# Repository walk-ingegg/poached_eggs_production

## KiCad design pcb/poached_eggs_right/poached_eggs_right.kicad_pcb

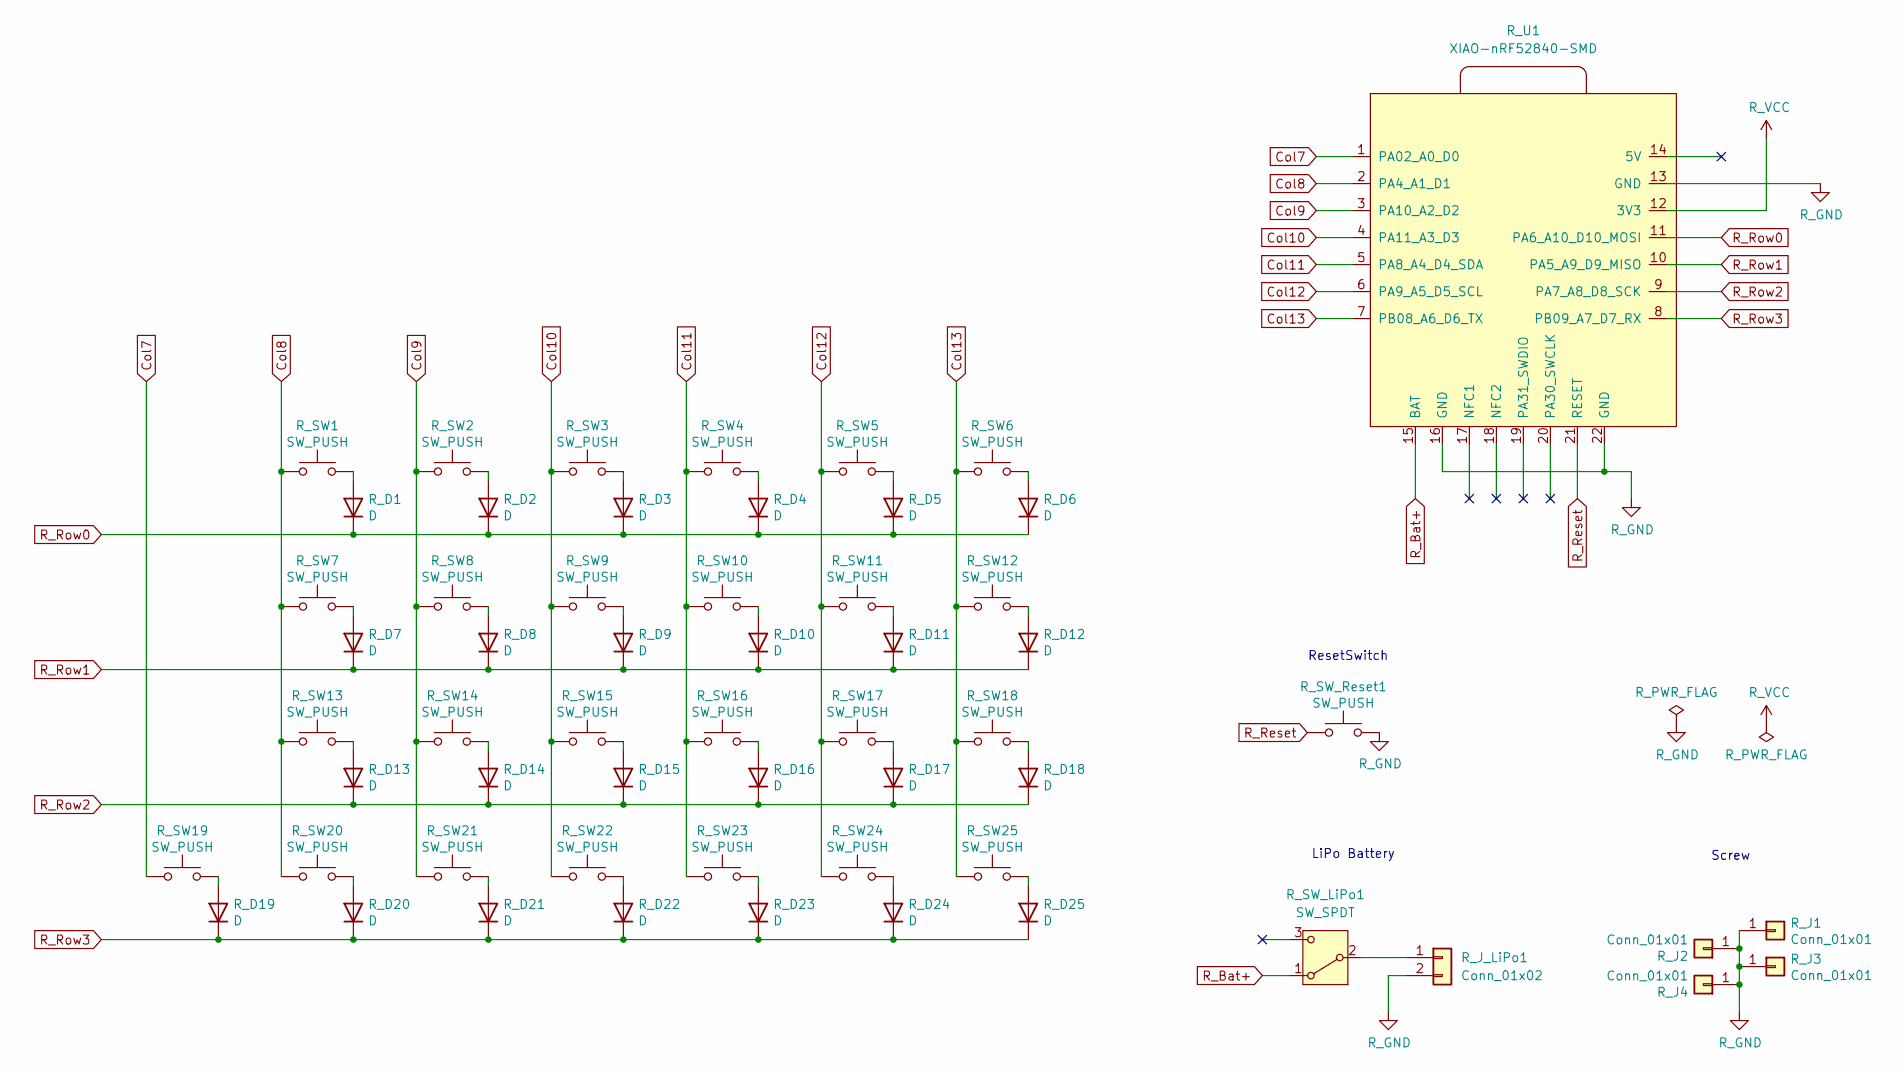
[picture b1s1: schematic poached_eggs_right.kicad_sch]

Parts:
R_D1, R_D2, R_D3, R_D4, R_D5, R_D6, R_D7, R_D8, R_D9, R_D10, R_D11, R_D12, R_D13, R_D14, R_D15, R_D16, R_D17, R_D18, R_D19, R_D20, R_D21, R_D22, R_D23, R_D24, R_D25: D; D_SOD-323
R_J1, R_J2, R_J3, R_J4: Conn_01x01; MountingHole_2.2mm_M2_ISO7380_Pad
R_J_LiPo1: Conn_01x02; JST_PH_S2B-PH-K_02x2.00mm_Angled_3d_wegg
R_SW1, R_SW2, R_SW3, R_SW4, R_SW5, R_SW6, R_SW7, R_SW8, R_SW9, R_SW10, R_SW11, R_SW12, R_SW13, R_SW14, R_SW15, R_SW16, R_SW17, R_SW18, R_SW19, R_SW20, R_SW21, R_SW22, R_SW23, R_SW24, R_SW25: SW_PUSH; Choc_v2_Hotswap_1u_17.5mm
R_SW_LiPo1: SW_SPDT; SW_Slide_SPDT_Angled_CK_OS102011MA1Q
R_SW_Reset1: SW_PUSH; SW_PUSH_1P1T_6x3.5mm_H4.3_APEM_MJTP1243_3d
R_U1: XIAO-nRF52840-SMD; XIAO-nRF52840-SMD_via

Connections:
Col7: R_SW19.1, R_U1.1 (PA02_A0_D0)
Col8: R_SW1.1, R_SW7.1, R_SW13.1, R_SW20.1, R_U1.2 (PA4_A1_D1)
Col9: R_SW2.1, R_SW8.1, R_SW14.1, R_SW21.1, R_U1.3 (PA10_A2_D2)
Col10: R_SW3.1, R_SW9.1, R_SW15.1, R_SW22.1, R_U1.4 (PA11_A3_D3)
Col11: R_SW4.1, R_SW10.1, R_SW16.1, R_SW23.1, R_U1.5 (PA8_A4_D4_SDA)
Col12: R_SW5.1, R_SW11.1, R_SW17.1, R_SW24.1, R_U1.6 (PA9_A5_D5_SCL)
Col13: R_SW6.1, R_SW12.1, R_SW18.1, R_SW25.1, R_U1.7 (PB08_A6_D6_TX)
unnamed: R_D1.2 (A), R_SW1.2
unnamed: R_D2.2 (A), R_SW2.2
unnamed: R_D3.2 (A), R_SW3.2
unnamed: R_D4.2 (A), R_SW4.2
unnamed: R_D5.2 (A), R_SW5.2
unnamed: R_D6.2 (A), R_SW6.2
unnamed: R_D7.2 (A), R_SW7.2
unnamed: R_D8.2 (A), R_SW8.2
unnamed: R_D9.2 (A), R_SW9.2
unnamed: R_D10.2 (A), R_SW10.2
unnamed: R_D11.2 (A), R_SW11.2
unnamed: R_D12.2 (A), R_SW12.2
unnamed: R_D13.2 (A), R_SW13.2
unnamed: R_D14.2 (A), R_SW14.2
unnamed: R_D15.2 (A), R_SW15.2
unnamed: R_D16.2 (A), R_SW16.2
unnamed: R_D17.2 (A), R_SW17.2
unnamed: R_D18.2 (A), R_SW18.2
unnamed: R_D19.2 (A), R_SW19.2
unnamed: R_D20.2 (A), R_SW20.2
unnamed: R_D21.2 (A), R_SW21.2
unnamed: R_D22.2 (A), R_SW22.2
unnamed: R_D23.2 (A), R_SW23.2
unnamed: R_D24.2 (A), R_SW24.2
unnamed: R_D25.2 (A), R_SW25.2
unnamed: R_J_LiPo1.1, R_SW_LiPo1.2 (B)
R_Bat+: R_SW_LiPo1.1 (A), R_U1.15 (BAT)
R_GND: R_J1.1, R_J2.1, R_J3.1, R_J4.1, R_J_LiPo1.2, R_SW_Reset1.2, R_U1.13 (GND), R_U1.16 (GND), R_U1.22 (GND)
R_Reset: R_SW_Reset1.1, R_U1.21 (RESET)
R_Row0: R_D1.1 (K), R_D2.1 (K), R_D3.1 (K), R_D4.1 (K), R_D5.1 (K), R_D6.1 (K), R_U1.11 (PA6_A10_D10_MOSI)
R_Row1: R_D7.1 (K), R_D8.1 (K), R_D9.1 (K), R_D10.1 (K), R_D11.1 (K), R_D12.1 (K), R_U1.10 (PA5_A9_D9_MISO)
R_Row2: R_D13.1 (K), R_D14.1 (K), R_D15.1 (K), R_D16.1 (K), R_D17.1 (K), R_D18.1 (K), R_U1.9 (PA7_A8_D8_SCK)
R_Row3: R_D19.1 (K), R_D20.1 (K), R_D21.1 (K), R_D22.1 (K), R_D23.1 (K), R_D24.1 (K), R_D25.1 (K), R_U1.8 (PB09_A7_D7_RX)
R_VCC: R_U1.12 (3V3)

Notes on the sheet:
Screw
LiPo Battery
ResetSwitch

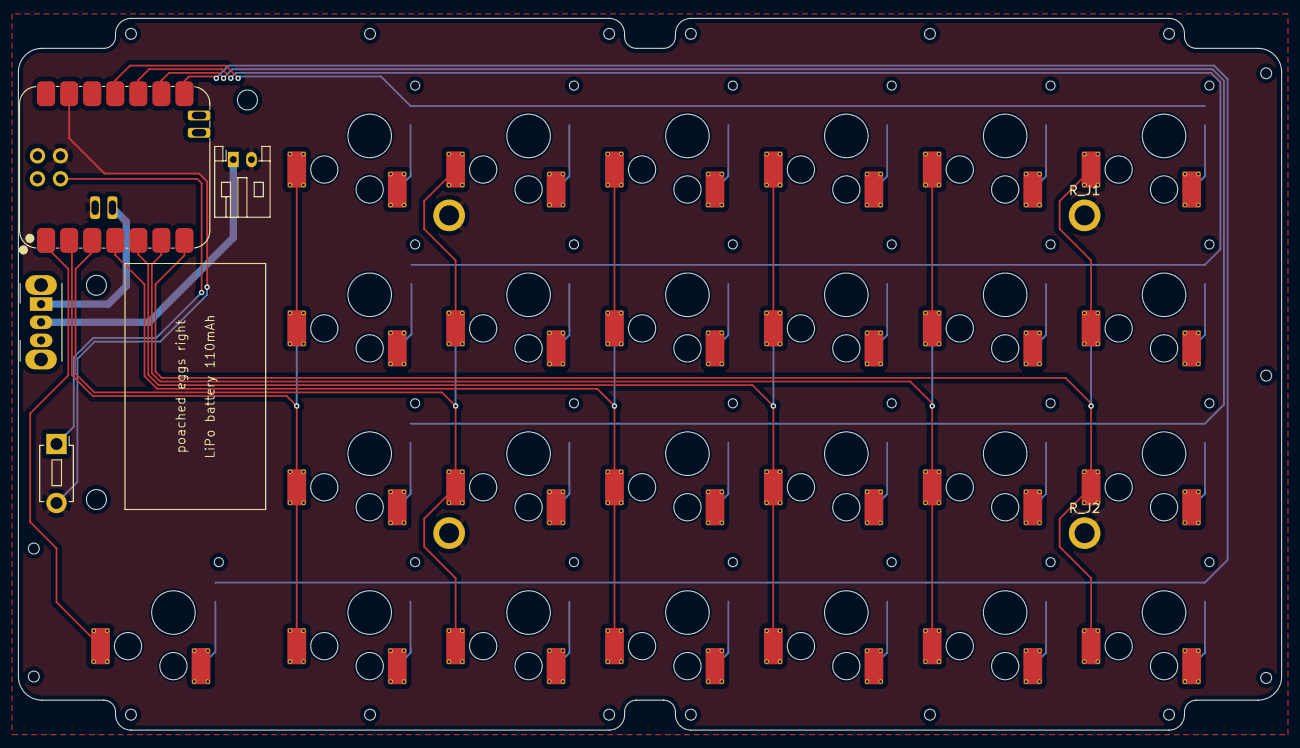
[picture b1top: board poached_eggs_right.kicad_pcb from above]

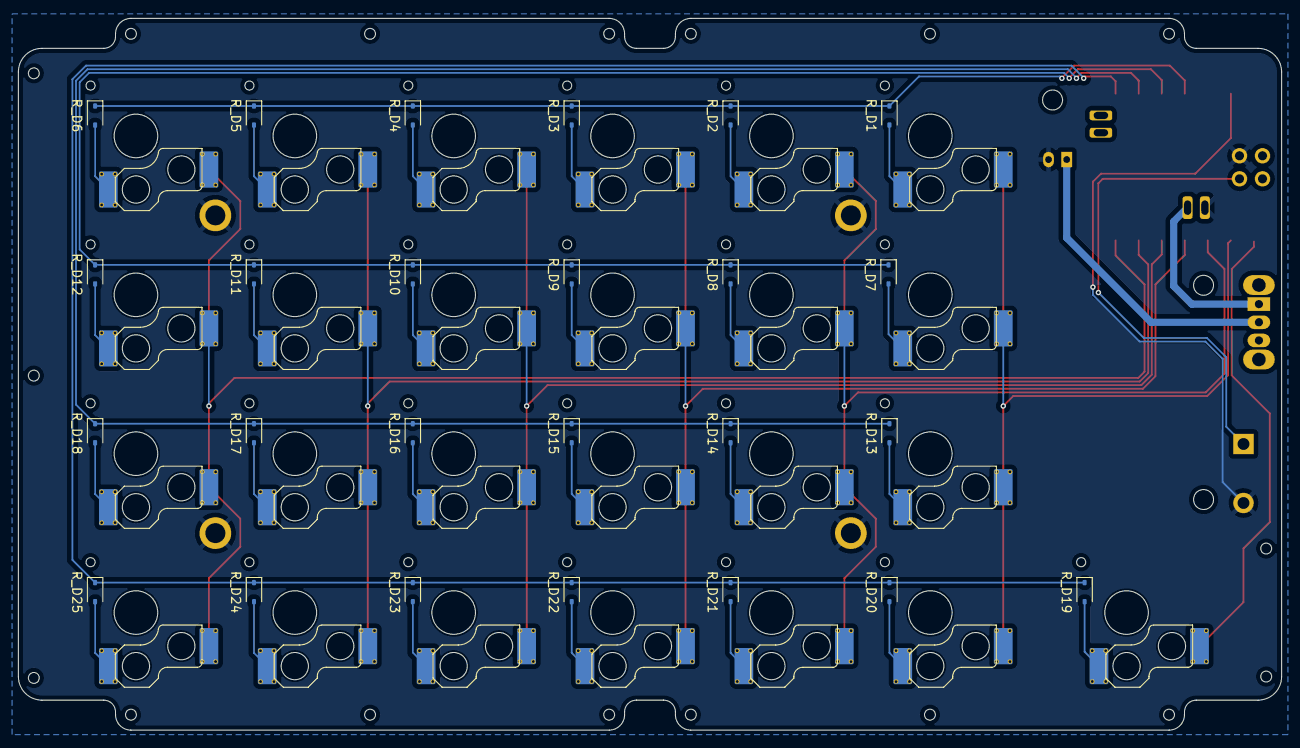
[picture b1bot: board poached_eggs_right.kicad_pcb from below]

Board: 2 copper layers, 139.1 x 78.3 mm, 58 parts (50 on the bottom side), 40 nets.

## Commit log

2024-09-01 init pcb kicad files
2024-09-08 init files
